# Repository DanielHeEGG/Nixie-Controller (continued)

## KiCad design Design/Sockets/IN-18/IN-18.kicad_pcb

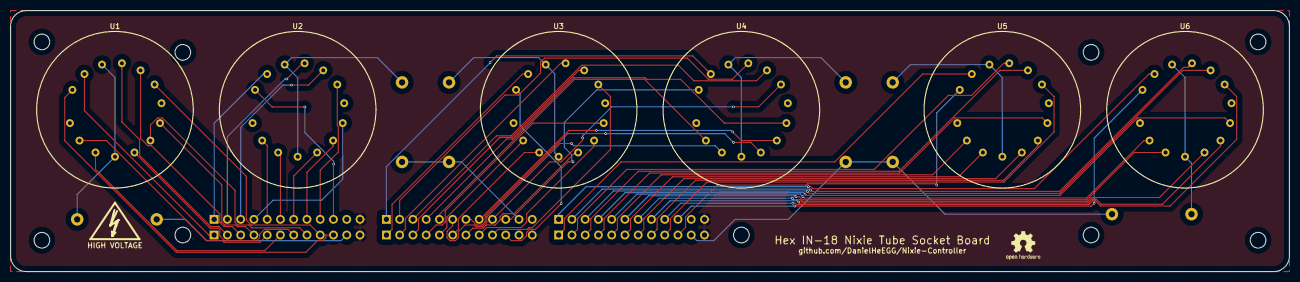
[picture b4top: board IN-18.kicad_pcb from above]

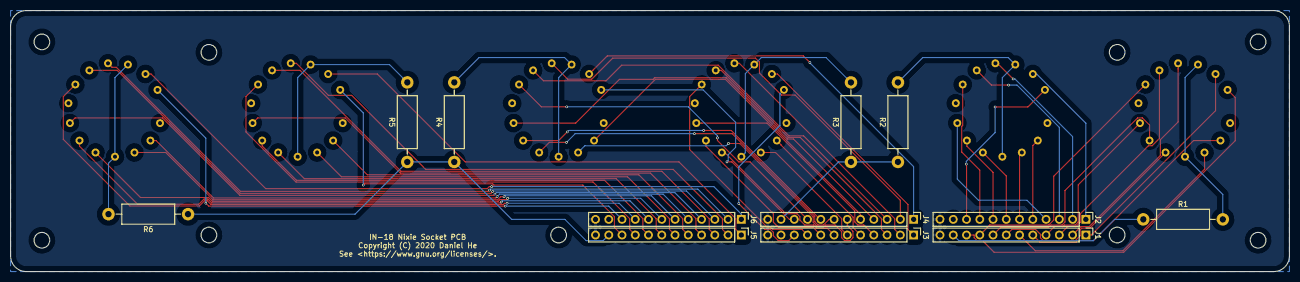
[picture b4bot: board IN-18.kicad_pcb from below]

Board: 2 copper layers, 245.0 x 50.0 mm, 18 parts (12 on the bottom side), 69 nets.

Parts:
J1, J2, J3, J4, J5, J6: Conn_01x12_Male; PinHeader_1x12_P2.54mm_Vertical
R1, R2, R3, R4, R5, R6: 3K; R_Axial_DIN0411_L9.9mm_D3.6mm_P15.24mm_Horizontal
U1, U2, U3, U4, U5, U6: IN-18

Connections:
Anode: R1.2, R2.2, R3.2, R4.2, R5.2, R6.2, U1.4, U1.12, U2.4, U2.12, U3.4, U3.12, U4.4, U4.12, U5.4, U5.12, U6.4, U6.12
GND: J1.12, J2.12, J3.12, J4.12, J5.12, J6.12
HV: J1.11, J2.11, J3.11, J4.11, J5.11, J6.11, R1.1, R2.1, R3.1, R4.1, R5.1, R6.1
unnamed: J1.1, U1.13
unnamed: J1.2, U1.11
unnamed: J1.3, U1.10
unnamed: J1.4, U1.7
unnamed: J1.5, U1.2
unnamed: J1.6, U1.3
unnamed: J1.7, U1.5
unnamed: J1.8, U1.6
unnamed: J1.9, U1.9
unnamed: J1.10, U1.14
unnamed: J2.1, U2.13
unnamed: J2.2, U2.11
unnamed: J2.3, U2.10
unnamed: J2.4, U2.7
unnamed: J2.5, U2.2
unnamed: J2.6, U2.3
unnamed: J2.7, U2.5
unnamed: J2.8, U2.6
unnamed: J2.9, U2.9
unnamed: J2.10, U2.14
unnamed: J3.1, U3.13
unnamed: J3.2, U3.11
unnamed: J3.3, U3.10
unnamed: J3.4, U3.7
unnamed: J3.5, U3.2
unnamed: J3.6, U3.3
unnamed: J3.7, U3.5
unnamed: J3.8, U3.6
unnamed: J3.9, U3.9
unnamed: J3.10, U3.14
unnamed: J4.1, U4.13
unnamed: J4.2, U4.11
unnamed: J4.3, U4.10
unnamed: J4.4, U4.7
unnamed: J4.5, U4.2
unnamed: J4.6, U4.3
unnamed: J4.7, U4.5
unnamed: J4.8, U4.6
unnamed: J4.9, U4.9
unnamed: J4.10, U4.14
unnamed: J5.1, U5.13
unnamed: J5.2, U5.11
unnamed: J5.3, U5.10
unnamed: J5.4, U5.7
unnamed: J5.5, U5.2
unnamed: J5.6, U5.3
unnamed: J5.7, U5.5
unnamed: J5.8, U5.6
unnamed: J5.9, U5.9
unnamed: J5.10, U5.14
unnamed: J6.1, U6.13
unnamed: J6.2, U6.11
unnamed: J6.3, U6.10
unnamed: J6.4, U6.7
unnamed: J6.5, U6.2
unnamed: J6.6, U6.3
unnamed: J6.7, U6.5
unnamed: J6.8, U6.6
unnamed: J6.9, U6.9
unnamed: J6.10, U6.14
unnamed: U1.1, U1.8
unnamed: U2.1, U2.8
unnamed: U3.1, U3.8
unnamed: U4.1, U4.8
unnamed: U5.1, U5.8
unnamed: U6.1, U6.8

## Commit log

2020-04-17 Add HV power supply
2020-04-20 Add potentiometer to allow variable output voltage
2020-04-21 Completed entire board (not tested yet)
2020-05-01 Remove feed forward cap for output stabillity
2020-05-01 Add ICSP for ucontroller, remove access to I2C
2020-05-01 Change file structure
2020-05-01 Seperate power supply files into different folder
2020-05-01 Add github link to controller, fix ground plane issues
2020-05-01 Add IN-18 nixie socket board
2020-05-01 Change pin header on controller from male to female
2020-05-04 Add software for controller
2020-05-05 Add battery mount to controller
2020-05-10 Add test code and remove comments in main software
2020-05-10 Add bypass caps for micro and RTC
2020-07-08 Reorganize project file structure
2020-07-17 Add part numbers to symbols in PowerSupply schematic for BOM
2020-07-17 Add part numbers to symbols in NixieController schematic for BOM
2020-07-18 Add program for initial time setup
2020-07-18 Create IN-8 socket board schematic & fabrication files
2020-07-18 Add front copper plane to IN-18 socket board, increase clearance, add high voltage warning symbol
2020-07-29 Fix IN-8 socket board orientation issue
2020-09-07 Remove BOM file which was accidentally included due to incorrect file type
2020-09-08 Add license notice to all human readable files
2021-01-22 Allow git tracking to exported BOM .csv files
2021-07-18 Add archive notice to readme
